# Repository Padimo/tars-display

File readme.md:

# TARS Quote

A miniature TARS with an OLED display that shows text that is sent to it via Firebase. 
A close friend of mine is a huge Interstellar fan, so I'm making this for her. 

### Features
- Show quote
	- From multiple people
	- Tracked with Firebase? I've used it before with ESP32 so should be straightforward
	- *Requires: ESP32, 0.96" OLED*
- Scroll if longer quotes
	- *Requires: EC11 rotary encoder (with button because why not)*

### Hardware

The TARS Quote device utilizes a three-part PCB. One part breaks out the USBC port so that it can be angled, a second is the main board with controls, and then the third board is a charlieplexed matrix of the TARS Braille dots.
The brains of this board is the ESP32S3-WROOM-1-N4. The display is a Waveshare SSD1331. The arms are moved by two standard blue 9g servos. Power and programming data come from USBC, and is stepped down using an AP2112K-3.3TRG. Standard 0805 LEDs and WS2818B LEDs compose the internal lighting of the system. Inputs come from a D-pad manufactured by Sparkfun. Speaker amplifier is a MAX98357A I2S IC.

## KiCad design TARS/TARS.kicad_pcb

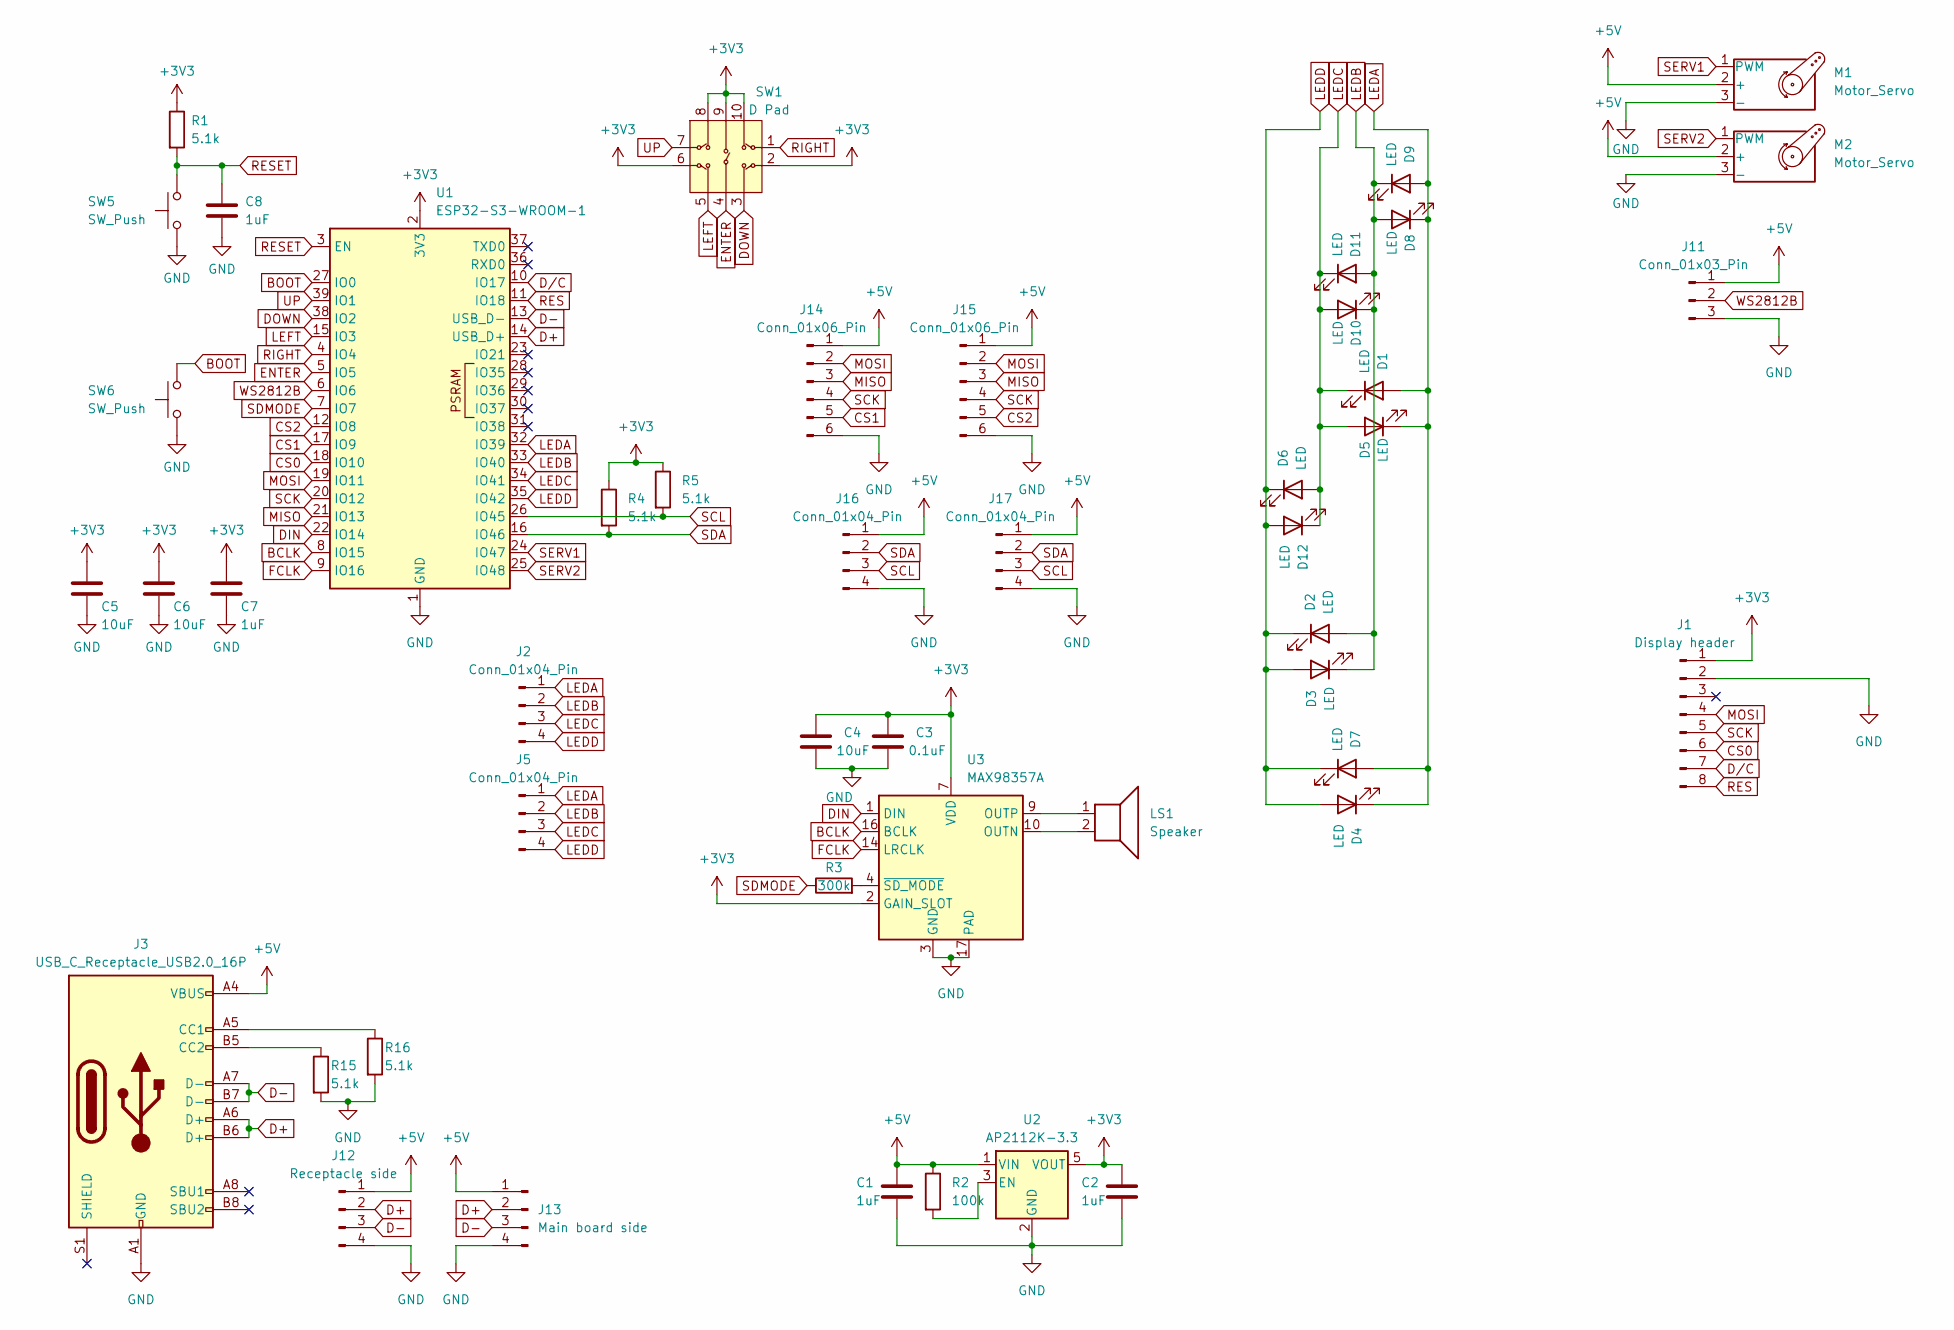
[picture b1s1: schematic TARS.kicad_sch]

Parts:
C1, C2, C7, C8: 1uF; C_0805_2012Metric
C3: 0.1uF; C_0805_2012Metric
C4, C5, C6: 10uF; C_0805_2012Metric
D1, D2, D3, D4, D5, D6, D7, D8, D9, D10, D11, D12: LED; LED_0805_2012Metric
J1: Display header; PinHeader_1x08_P2.54mm_Vertical
J2, J5, J16, J17: Conn_01x04_Pin; PinHeader_1x04_P2.54mm_Vertical
J3: USB_C_Receptacle_USB2.0_16P; USB_C_Receptacle_GCT_USB4085
J11: Conn_01x03_Pin; PinHeader_1x03_P2.54mm_Vertical
J12: Receptacle side; PinHeader_1x04_P2.54mm_Vertical
J13: Main board side; PinHeader_1x04_P2.54mm_Horizontal
J14, J15: Conn_01x06_Pin; PinHeader_1x06_P2.54mm_Vertical
LS1: Speaker; PinHeader_1x02_P2.54mm_Vertical
M1, M2: Motor_Servo; PinHeader_1x03_P2.54mm_Vertical
R1, R4, R5, R15, R16: 5.1k; R_0805_2012Metric
R2: 100k; R_0805_2012Metric
R3: 300k; R_0805_2012Metric
SW1: D Pad; COM-26850 D Pad
SW5, SW6: SW_Push; SW_Push_1P1T_NO_CK_KSC6xxJ
U1: ESP32-S3-WROOM-1
U2: AP2112K-3.3; SOT-23-5
U3: MAX98357A; TQFN-16-1EP_3x3mm_P0.5mm_EP1.23x1.23mm

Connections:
+3V3: C2.1, C3.1, C4.1, C5.1, C6.1, C7.1, J1.1, R1.1, R4.1, R5.1, SW1.2, SW1.6, SW1.8, SW1.9, SW1.10, U1.2 (3V3), U2.5 (VOUT), U3.2 (GAIN_SLOT), U3.7 (VDD), U3.8 (VDD)
+5V: C1.1, J3.A4 (VBUS), J3.A9 (VBUS), J3.B4 (VBUS), J3.B9 (VBUS), J11.1, J12.1, J13.1, J14.1, J15.1, J16.1, J17.1, M1.2 (+), M2.2 (+), R2.1, U2.1 (VIN)
BCLK: U1.8 (IO15), U3.16 (BCLK)
BOOT: SW6.2, U1.27 (IO0)
CS0: J1.6, U1.18 (IO10)
CS1: J14.5, U1.17 (IO9)
CS2: J15.5, U1.12 (IO8)
D+: J3.A6 (D+), J3.B6 (D+), J12.2, J13.2, U1.14 (USB_D+)
D-: J3.A7 (D-), J3.B7 (D-), J12.3, J13.3, U1.13 (USB_D-)
DIN: U1.22 (IO14), U3.1 (DIN)
DOWN: SW1.3, U1.38 (IO2)
D/C: J1.7, U1.10 (IO17)
ENTER: SW1.4, U1.5 (IO5)
FCLK: U1.9 (IO16), U3.14 (LRCLK)
GND: C1.2, C2.2, C3.2, C4.2, C5.2, C6.2, C7.2, C8.2, J1.2, J3.A1 (GND), J3.A12 (GND), J3.B1 (GND), J3.B12 (GND), J11.3, J12.4, J13.4, J14.6, J15.6, J16.4, J17.4, M1.3 (-), M2.3 (-), R15.2, R16.2, SW5.1, SW6.1, U1.1 (GND), U1.40 (GND), U1.41 (GND), U2.2 (GND), U3.3 (GND), U3.11 (GND), U3.15 (GND), U3.17 (PAD)
LEDA: D1.2 (A), D4.1 (K), D5.1 (K), D7.2 (A), D8.1 (K), D9.2 (A), J2.1, J5.1, U1.32 (IO39)
LEDB: D2.2 (A), D3.1 (K), D8.2 (A), D9.1 (K), D10.1 (K), D11.2 (A), J2.2, J5.2, U1.33 (IO40)
LEDC: D1.1 (K), D5.2 (A), D6.2 (A), D10.2 (A), D11.1 (K), D12.1 (K), J2.3, J5.3, U1.34 (IO41)
LEDD: D2.1 (K), D3.2 (A), D4.2 (A), D6.1 (K), D7.1 (K), D12.2 (A), J2.4, J5.4, U1.35 (IO42)
LEFT: SW1.5, U1.15 (IO3)
MISO: J14.3, J15.3, U1.21 (IO13)
MOSI: J1.4, J14.2, J15.2, U1.19 (IO11)
unnamed: J3.A5 (CC1), R16.1
unnamed: J3.B5 (CC2), R15.1
unnamed: R2.2, U2.3 (EN)
unnamed: LS1.2, U3.10 (OUTN)
unnamed: LS1.1, U3.9 (OUTP)
unnamed: R3.2, U3.4 (~SD_MODE)
RES: J1.8, U1.11 (IO18)
RESET: C8.1, R1.2, SW5.2, U1.3 (EN)
RIGHT: SW1.1, U1.4 (IO4)
SCK: J1.5, J14.4, J15.4, U1.20 (IO12)
SCL: J16.3, J17.3, R5.2, U1.26 (IO45)
SDA: J16.2, J17.2, R4.2, U1.16 (IO46)
SDMODE: R3.1, U1.7 (IO7)
SERV1: M1.1 (PWM), U1.24 (IO47)
SERV2: M2.1 (PWM), U1.25 (IO48)
UP: SW1.7, U1.39 (IO1)
WS2812B: J11.2, U1.6 (IO6)

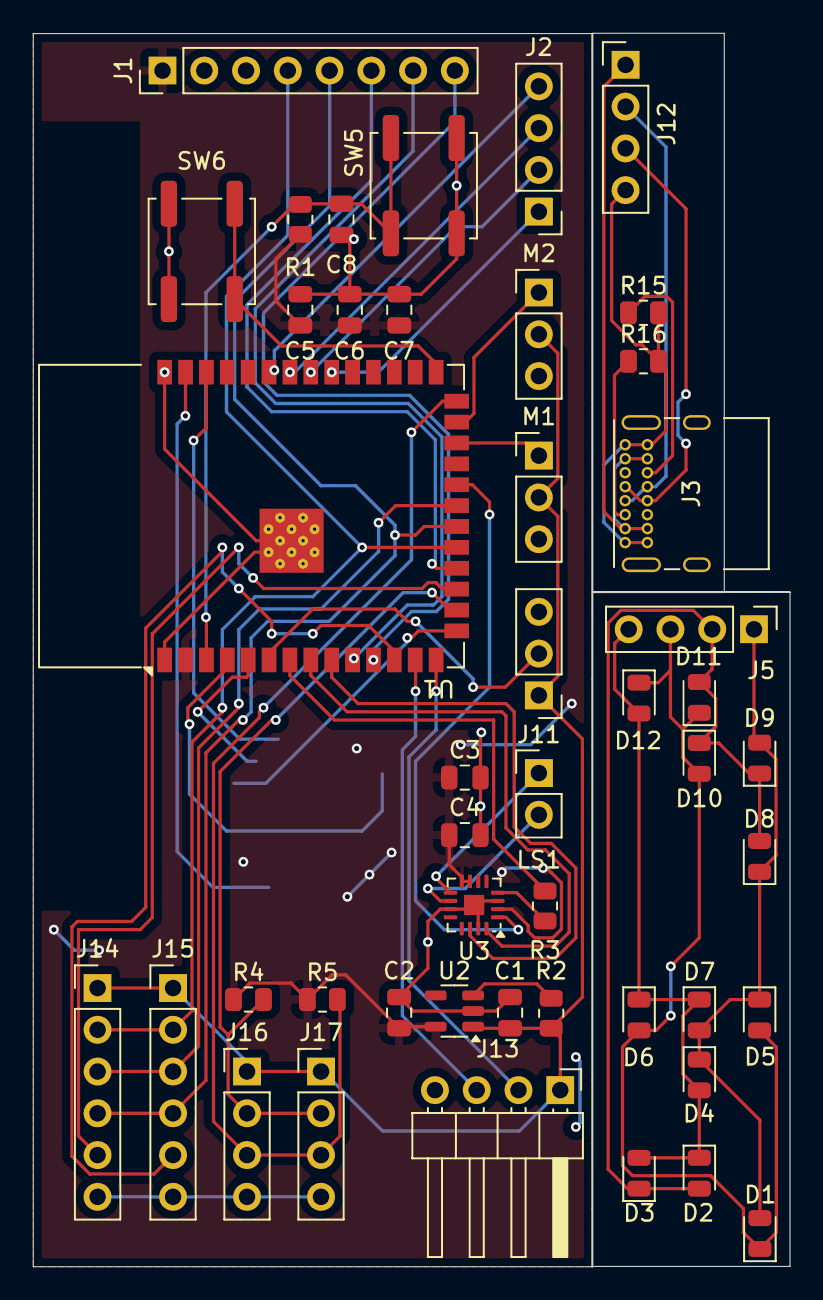
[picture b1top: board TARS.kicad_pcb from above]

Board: 2 copper layers, 46.0 x 75.0 mm, 47 parts (1 on the bottom side), 39 nets.

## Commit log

2025-10-04 Readme and journal
2025-10-05 Update readme with features
2025-10-06 Add first iteration of CAD to repo
2025-12-16 add everything
2025-12-16 Update Gerber
2025-12-16 update BOM
2025-12-16 update BOM, found d pad on digikey
2025-12-16 update mousebites
2025-12-17 update BOM with prices
2025-12-17 update gerbers and readme
2025-12-17 added PDF schematic
2025-12-17 added initial OTA firmware
2025-12-17 fix bom
2025-12-17 add exploded CAD view to readme
2025-12-18 full assembly
2026-01-05 update pcb (remove mouse bites)
2026-01-05 pcb silkscreen separation
